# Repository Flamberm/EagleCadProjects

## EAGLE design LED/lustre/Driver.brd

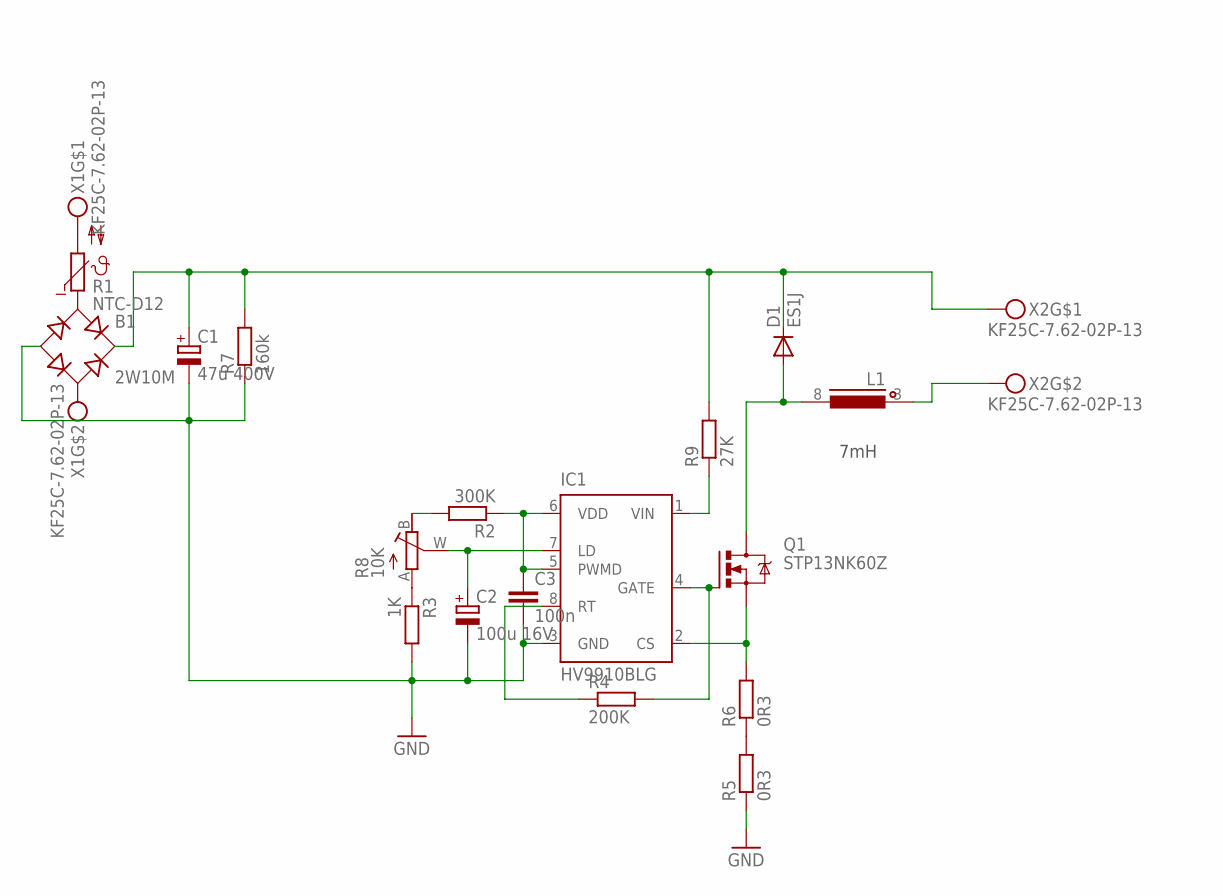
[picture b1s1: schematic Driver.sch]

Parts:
B1: 2W10M; RB1A
C1: 47u 400V; E7,5-16-32-HORIZ
C2: 100u 16V; E2,5-6
C3: 100n; C0805
D1: ES1J; DO214AC
IC1: HV9910BLG; SOIC-08LG
L1: INDUCTOREE20V; EE20_10PIN
Q1: STP13NK60Z; TO220BV
R1: NTC-D12
R2: 300K; R0805
R3: 1K; R0805
R4: 200K; R0805
R5, R6: 0R3; 0414/15
R7: 160k; 0204/7
R8: 10K; RJ9W
R9: 27K; P0613/15
X1, X2: KF25C-7.62-02P-13

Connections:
300V: B1.+, C1.+, D1.C, R7.2, R9.2, X2.P$1
GND: B1.-, C1.-, C2.-, C3.2, IC1.3 (GND), R3.2, R5.1, R7.1
unnamed: C3.1, IC1.5 (PWMD), IC1.6 (VDD), R2.1
unnamed: R1.2, X1.P$1
unnamed: B1.AC2, X1.P$2
unnamed: B1.AC1, R1.1
unnamed: L1.3 (1), X2.P$2
unnamed: C2.+, IC1.7 (LD), R8.W (S)
unnamed: D1.A, L1.8 (2), Q1.D
unnamed: IC1.8 (RT), R4.1
unnamed: IC1.4 (GATE), Q1.G, R4.2
unnamed: R5.2, R6.1
unnamed: IC1.2 (CS), Q1.S, R6.2
unnamed: R3.1, R8.A
unnamed: R2.2, R8.B (E)
unnamed: IC1.1 (VIN), R9.1

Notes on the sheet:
7mH

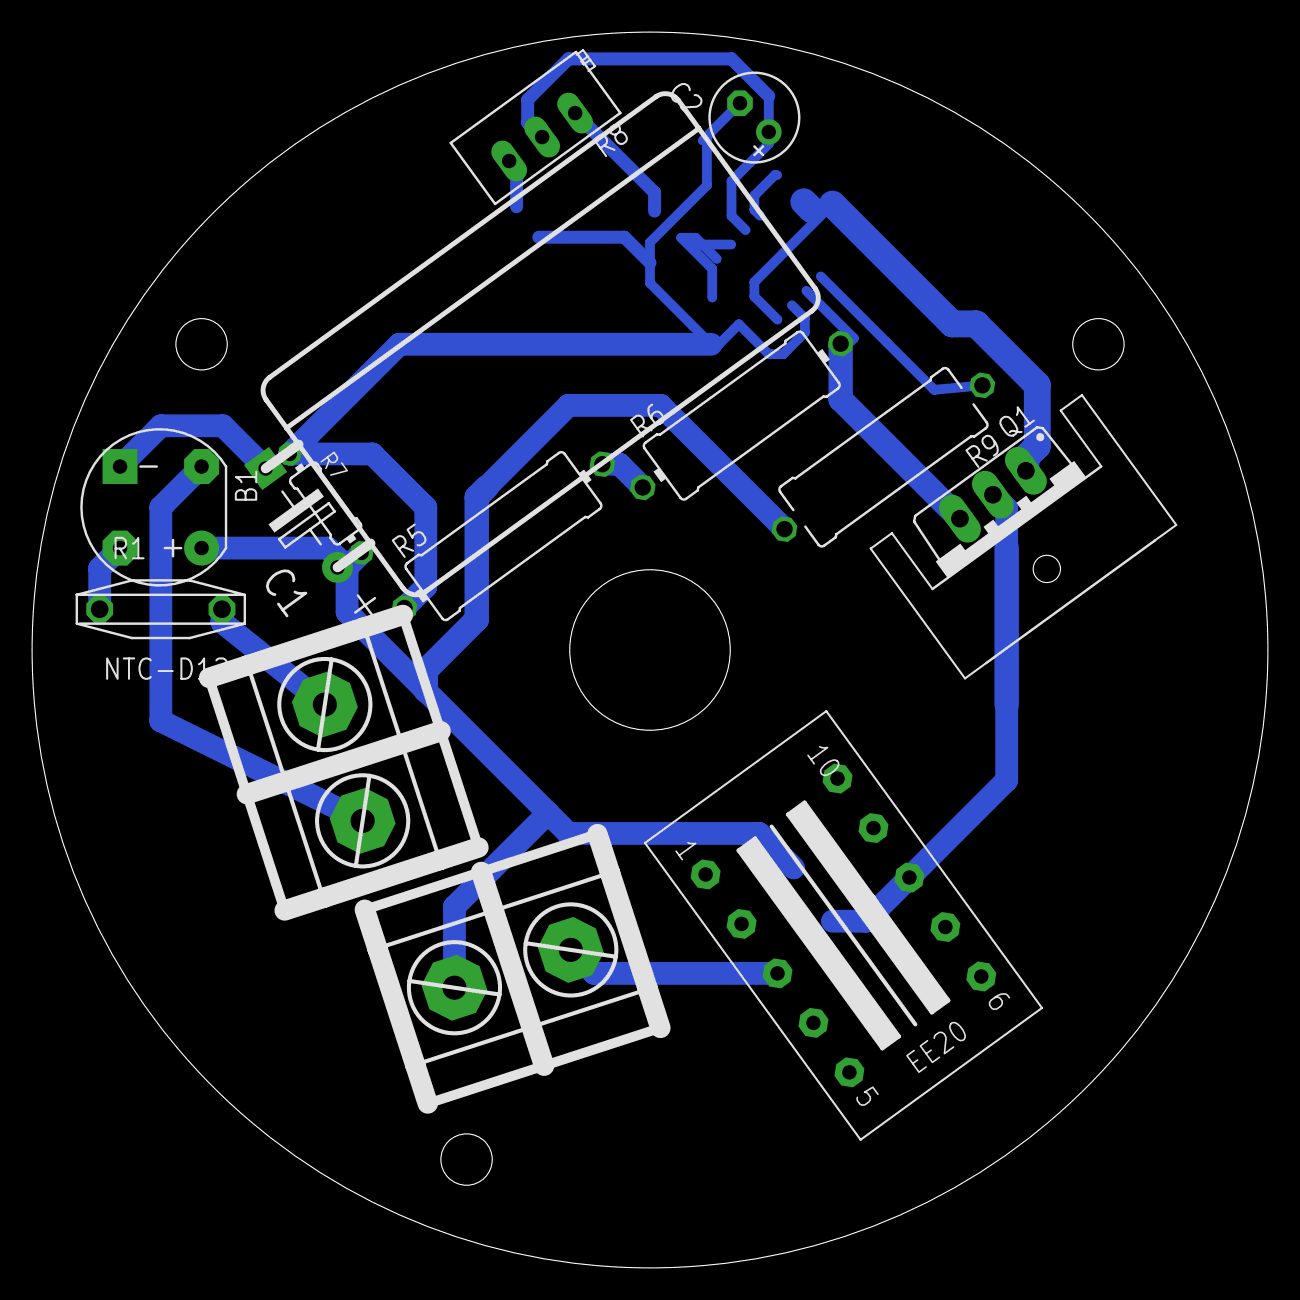
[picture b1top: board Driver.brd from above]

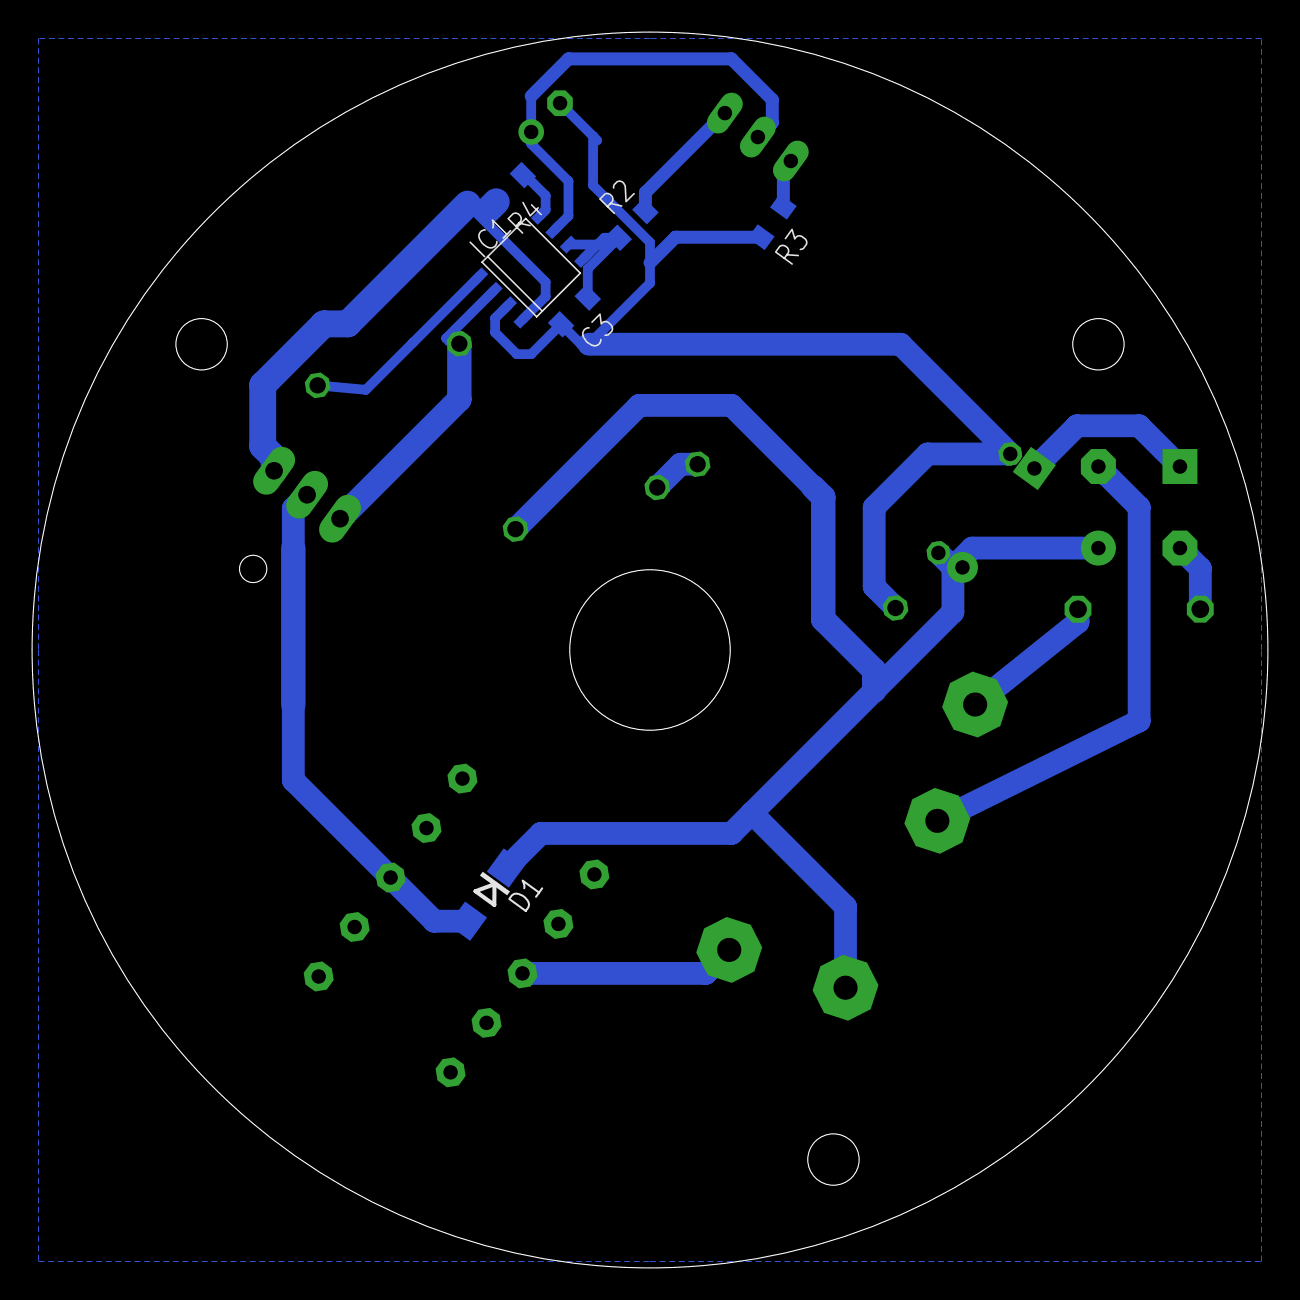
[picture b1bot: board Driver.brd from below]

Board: 2 copper layers, 77.0 x 77.0 mm, 20 parts (6 on the bottom side), 16 nets.

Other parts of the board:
U$1: SK95-3M3_HOLE

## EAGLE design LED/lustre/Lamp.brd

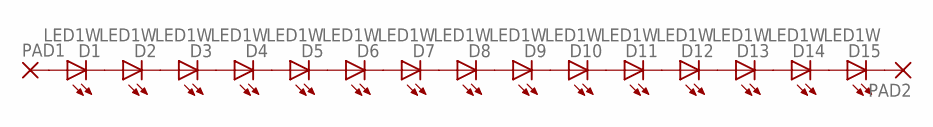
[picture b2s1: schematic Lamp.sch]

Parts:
D1, D2, D3, D4, D5, D6, D7, D8, D9, D10, D11, D12, D13, D14, D15: LED1W; LED-1W
PAD1, PAD2: 3,81/1,4

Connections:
unnamed: D1.K (C), D2.A
unnamed: D2.K (C), D3.A
unnamed: D3.K (C), D4.A
unnamed: D4.K (C), D5.A
unnamed: D5.K (C), D6.A
unnamed: D6.K (C), D7.A
unnamed: D7.K (C), D8.A
unnamed: D8.K (C), D9.A
unnamed: D9.K (C), D10.A
unnamed: D1.A, PAD1.1
unnamed: D10.K (C), D11.A
unnamed: D11.K (C), D12.A
unnamed: D12.K (C), D13.A
unnamed: D13.K (C), D14.A
unnamed: D14.K (C), D15.A
unnamed: D15.K (C), PAD2.1

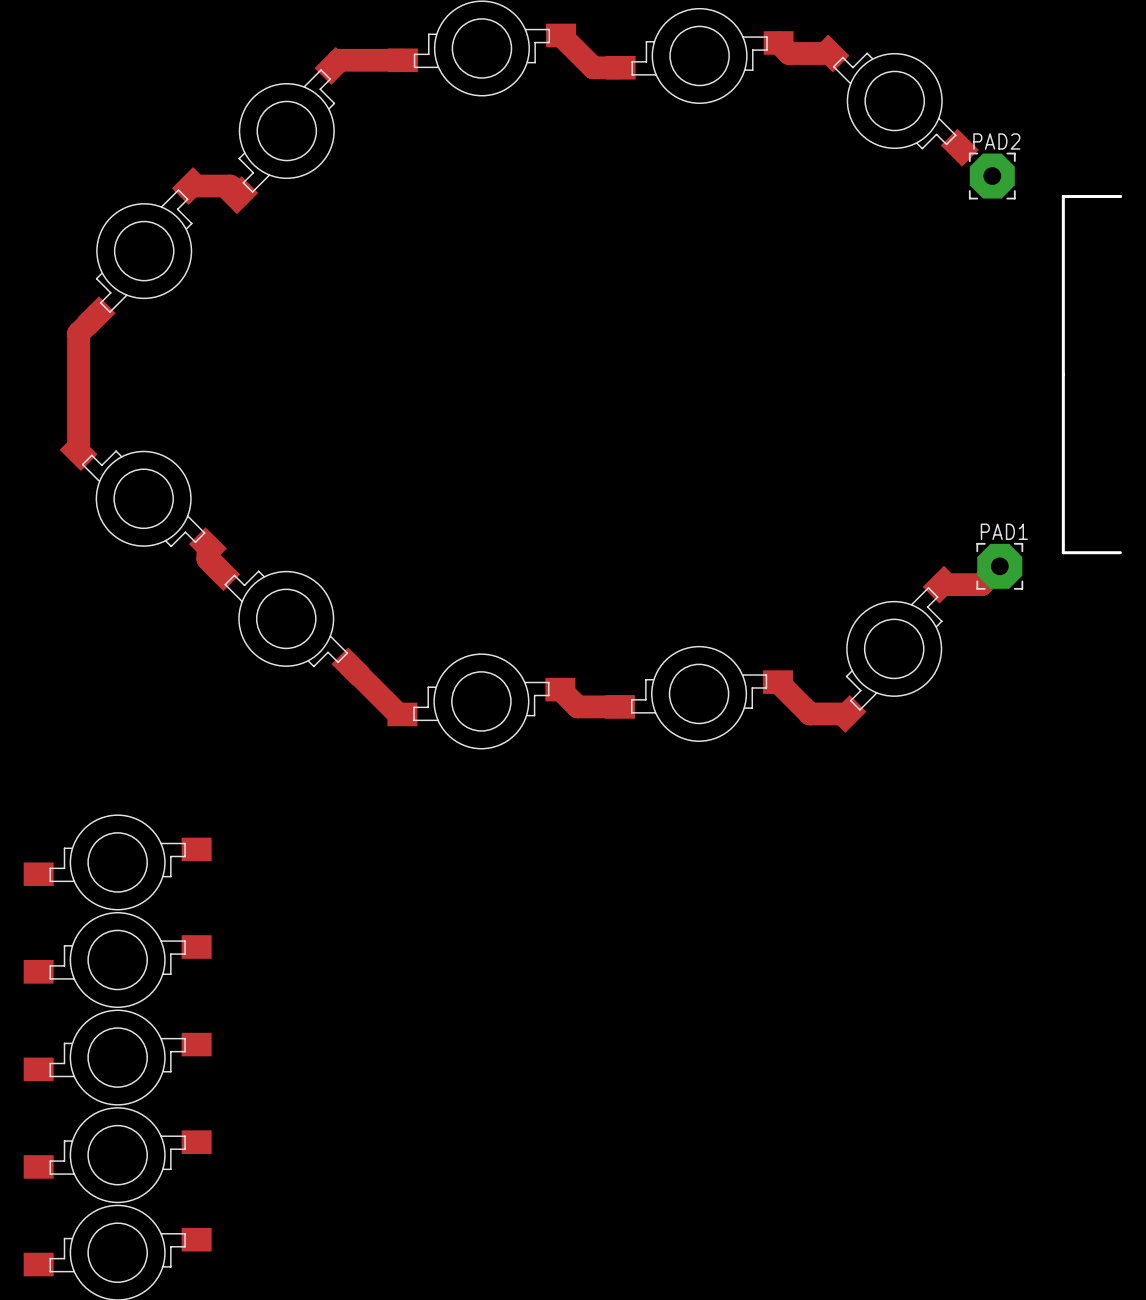
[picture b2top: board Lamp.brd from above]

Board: 2 copper layers, 17 parts (0 on the bottom side), 16 nets.

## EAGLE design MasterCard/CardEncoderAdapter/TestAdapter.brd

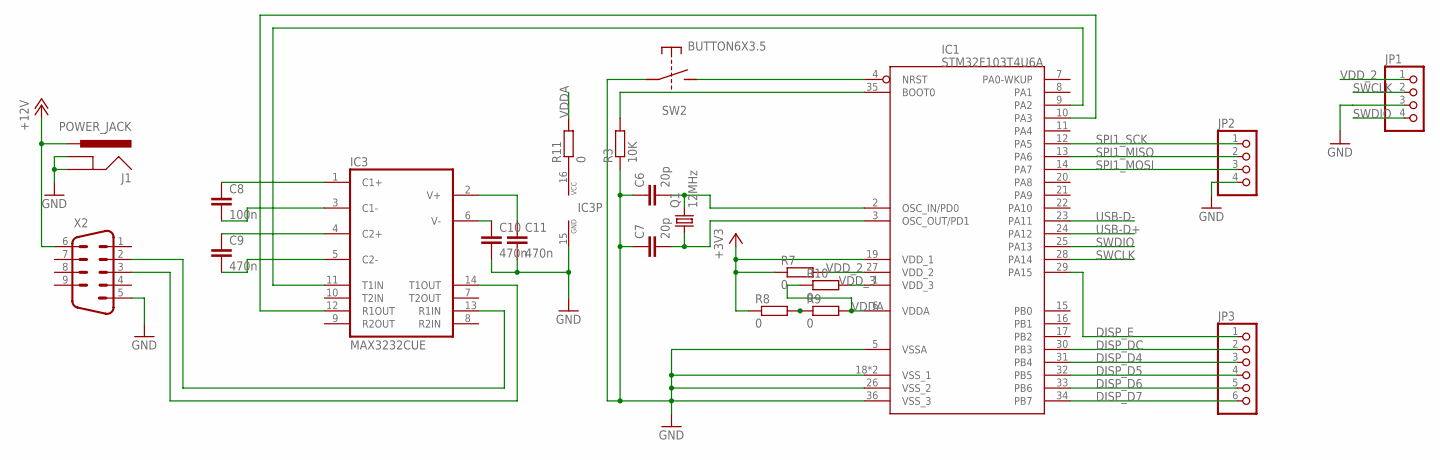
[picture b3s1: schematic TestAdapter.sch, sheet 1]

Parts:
C6, C7: 20p; CAP0805
C8: 100n; CAP0805
C9, C10, C11: 470n; CAP0805
IC1: STM32F103T4U6A; QFN50P606X606X100-36
IC3: MAX3232CUE; TSSOP16
J1: POWER_JACK; POWER_JACK_PTH
JP1, JP2: PINHD-1X4; 1X04
JP3: PINHD-1X6; 1X06
Q1: 12MHz; CRYSTAL-5025
R3: 10K; RESC2012X50
R7, R8, R9, R10, R11: 0; RESC2012X50
SW2: BUTTON6X3.5; SW-6X3.5
X2: M09-182; 182-009-MALE

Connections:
+3V3: IC1.19 (VDD_1), R7.1, R8.1; also elsewhere on the board
+12V: J1.PWR, X2.6
DISP_D4: IC1.31 (PB4), JP3.3
DISP_D5: IC1.32 (PB5), JP3.4
DISP_D6: IC1.33 (PB6), JP3.5
DISP_D7: IC1.34 (PB7), JP3.6
DISP_DC: IC1.30 (PB3), JP3.2
DISP_E: IC1.29 (PA15), JP3.1
GND: C6.1, C7.1, C10.2, C11.2, IC1.5 (VSSA), IC1.18 (VSS_1), IC1.26 (VSS_2), IC1.36 (VSS_3), IC1.P$1 (VSS_1), IC3.15 (GND), J1.GND, J1.GNDBREAK, JP1.3, JP2.4, R3.1, SW2.1, X2.5; also elsewhere on the board
unnamed: C7.2, IC1.3 (OSC_OUT/PD1), Q1.P$1 (1)
unnamed: C6.2, IC1.2 (OSC_IN/PD0), Q1.P$2 (2)
unnamed: IC1.35 (BOOT0), R3.2
unnamed: IC1.4 (NRST), SW2.2
unnamed: IC3.16 (VCC), R11.1
unnamed: R8.2, R9.1
unnamed: IC1.9 (PA2), IC3.11 (T1IN)
unnamed: IC1.10 (PA3), IC3.12 (R1OUT)
unnamed: IC3.14 (T1OUT), X2.3
unnamed: IC3.13 (R1IN), X2.2
unnamed: C8.1, IC3.1 (C1+)
unnamed: C8.2, IC3.3 (C1-)
unnamed: C9.1, IC3.4 (C2+)
unnamed: C9.2, IC3.5 (C2-)
unnamed: C11.1, IC3.2 (V+)
unnamed: C10.1, IC3.6 (V-)
SPI1_MISO: IC1.13 (PA6), JP2.2
SPI1_MOSI: IC1.14 (PA7), JP2.3
SPI1_SCK: IC1.12 (PA5), JP2.1
SWCLK: IC1.28 (PA14), JP1.2
SWDIO: IC1.25 (PA13), JP1.4
USB-D+: IC1.24 (PA12); also elsewhere on the board
USB-D-: IC1.23 (PA11); also elsewhere on the board
VDDA: IC1.6 (VDDA), R9.2, R10.1, R11.2
VDD_2: IC1.27 (VDD_2), JP1.1, R7.2; also elsewhere on the board
VDD_3: IC1.1 (VDD_3), R10.2; also elsewhere on the board

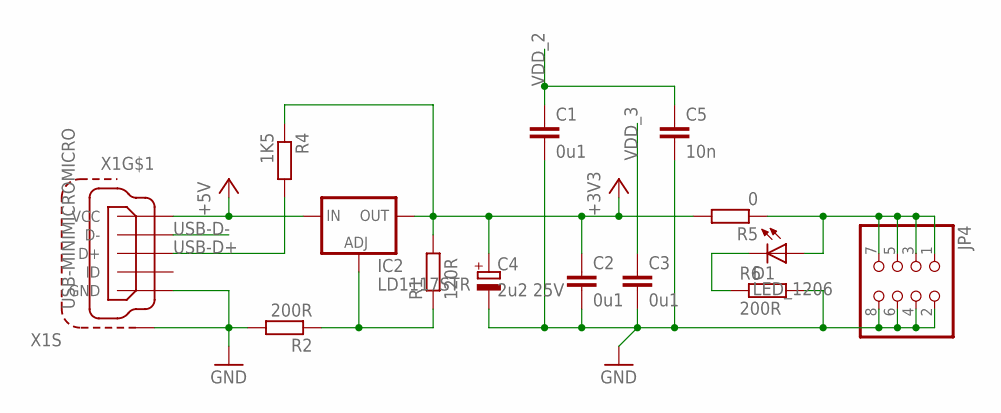
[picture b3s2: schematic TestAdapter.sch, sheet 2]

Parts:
C1, C2, C3: 0u1; CAP0805
C4: 2u2 25V; CAPMP3317X180
C5: 10n; CAP0805
D1: LED_1206; LED1206
IC2: LD1117STR; SOT230P700X180-4
JP4: PINHD-2X4; 2X04
R1: 120R; RESC2012X50
R2, R6: 200R; RESC2012X50
R4: 1K5; RESC2012X50
R5: 0; RESC2012X50
X1: USB-MINIMICROMICRO; USB-B-MICRO-SMD

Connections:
+3V3: C2.1, C4.1 (+), IC2.2 (OUT), IC2.4 (OUT), R1.2, R4.1, R5.2; also elsewhere on the board
+5V: IC2.3 (IN), X1.VBUS (VCC)
GND: C1.2, C2.2, C3.2, C4.2 (-), C5.2, JP4.2, JP4.4, JP4.6, JP4.8, R2.2, R6.2, X1.GND, X1.SHIELD1 (S1), X1.SHIELD2 (S1), X1.SHIELD3 (S1); also elsewhere on the board
unnamed: IC2.1 (ADJ), R1.1, R2.1
unnamed: D1.A, JP4.1, JP4.3, JP4.5, JP4.7, R5.1
unnamed: D1.C, R6.1
USB-D+: R4.2, X1.D+; also elsewhere on the board
USB-D-: X1.D-; also elsewhere on the board
VDD_2: C1.1, C5.1; also elsewhere on the board
VDD_3: C3.1; also elsewhere on the board

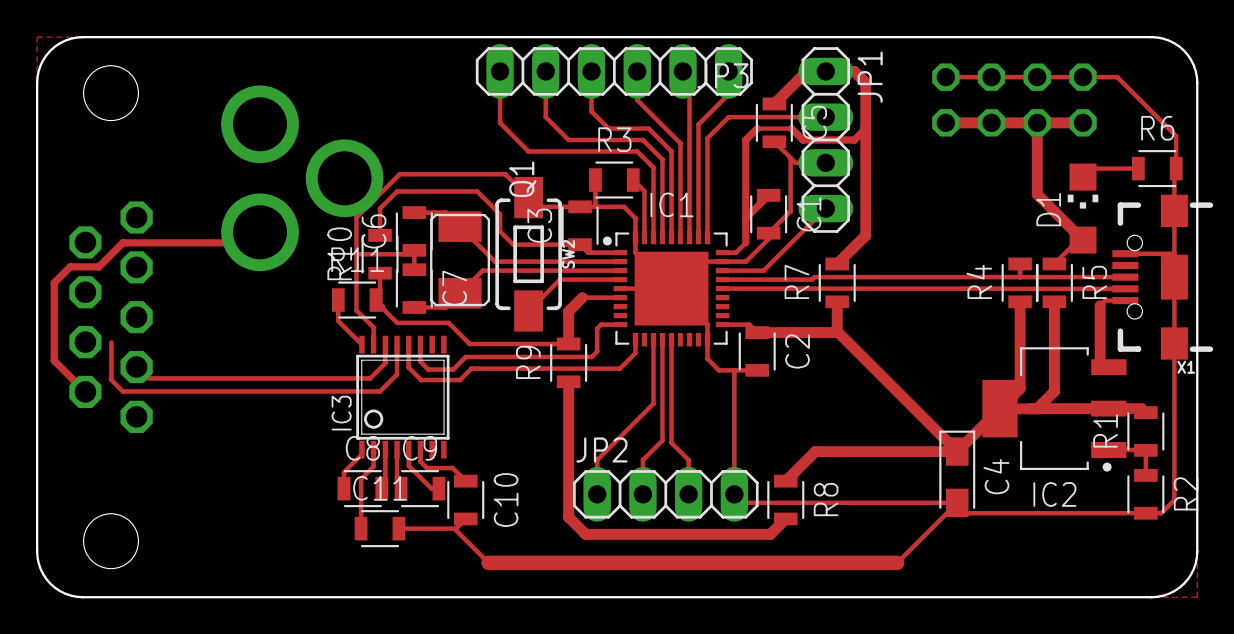
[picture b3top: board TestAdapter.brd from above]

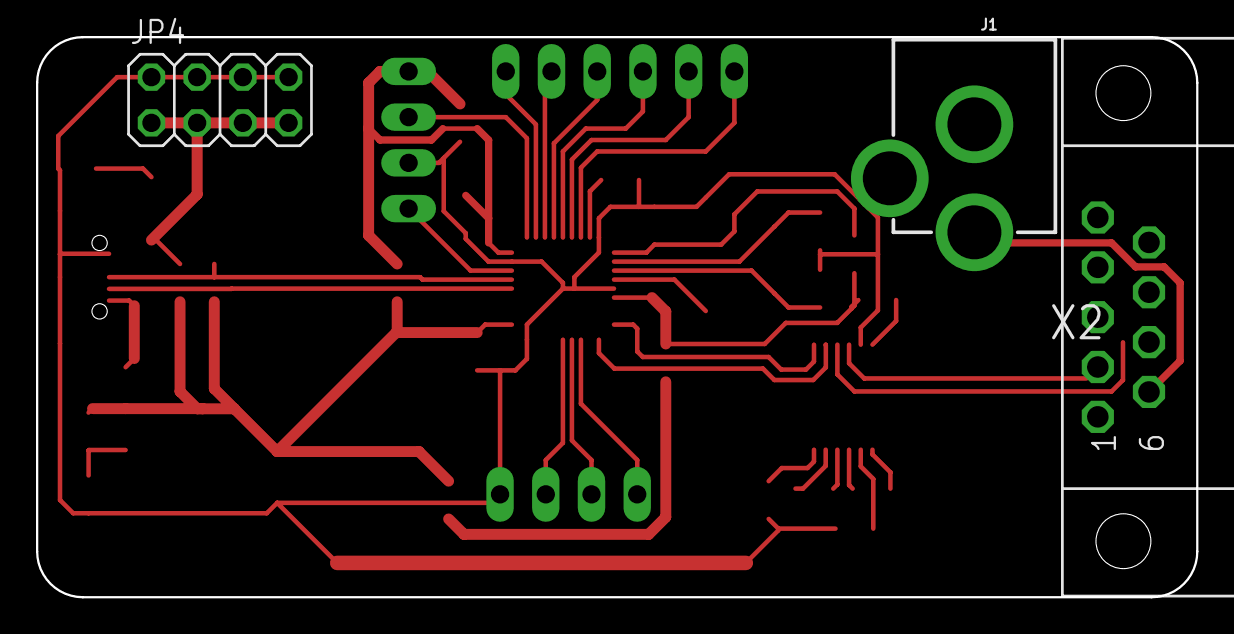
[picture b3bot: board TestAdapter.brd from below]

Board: 2 copper layers, 64.5 x 31.1 mm, 35 parts (3 on the bottom side), 39 nets.

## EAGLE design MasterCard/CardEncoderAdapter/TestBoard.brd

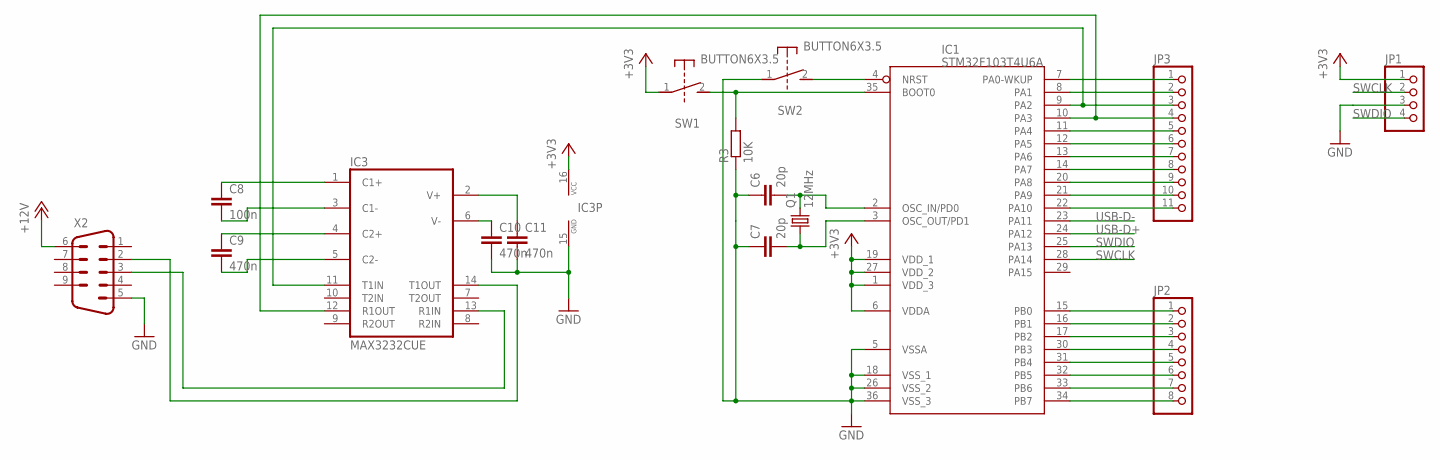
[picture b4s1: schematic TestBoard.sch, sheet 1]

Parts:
C6, C7: 20p; CAP0805
C8: 100n; CAP0805
C9, C10, C11: 470n; CAP0805
IC1: STM32F103T4U6A; QFN50P606X606X100-36
IC3: MAX3232CUE; TSSOP16
JP1: PINHD-1X4; 1X04
JP2: PINHD-1X8; 1X08
JP3: PINHD-1X11; 1X11
Q1: 12MHz; HC49UP
R3: 10K; RESC2012X50
SW1, SW2: BUTTON6X3.5; SW-6X3.5
X2: M09-182; 182-009-MALE

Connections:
+3V3: IC1.1 (VDD_3), IC1.6 (VDDA), IC1.19 (VDD_1), IC1.27 (VDD_2), IC3.16 (VCC), JP1.1, SW1.1; also elsewhere on the board
+12V: X2.6
GND: C6.1, C7.1, C10.2, C11.2, IC1.5 (VSSA), IC1.18 (VSS_1), IC1.26 (VSS_2), IC1.36 (VSS_3), IC3.15 (GND), JP1.3, R3.1, SW2.1, X2.5; also elsewhere on the board
unnamed: C7.2, IC1.3 (OSC_OUT/PD1), Q1.1
unnamed: C6.2, IC1.2 (OSC_IN/PD0), Q1.2
unnamed: IC1.35 (BOOT0), R3.2, SW1.2
unnamed: IC1.4 (NRST), SW2.2
unnamed: IC1.15 (PB0), JP2.1
unnamed: IC1.16 (PB1), JP2.2
unnamed: IC1.17 (PB2), JP2.3
unnamed: IC1.30 (PB3), JP2.4
unnamed: IC1.31 (PB4), JP2.5
unnamed: IC1.32 (PB5), JP2.6
unnamed: IC1.33 (PB6), JP2.7
unnamed: IC1.34 (PB7), JP2.8
unnamed: IC1.7 (PA0-WKUP), JP3.1
unnamed: IC1.8 (PA1), JP3.2
unnamed: IC1.9 (PA2), IC3.11 (T1IN), JP3.3
unnamed: IC1.10 (PA3), IC3.12 (R1OUT), JP3.4
unnamed: IC1.11 (PA4), JP3.5
unnamed: IC1.12 (PA5), JP3.6
unnamed: IC1.13 (PA6), JP3.7
unnamed: IC1.14 (PA7), JP3.8
unnamed: IC1.20 (PA8), JP3.9
unnamed: IC1.21 (PA9), JP3.10
unnamed: IC1.22 (PA10), JP3.11
unnamed: IC3.14 (T1OUT), X2.2
unnamed: IC3.13 (R1IN), X2.3
unnamed: C8.1, IC3.1 (C1+)
unnamed: C8.2, IC3.3 (C1-)
unnamed: C9.1, IC3.4 (C2+)
unnamed: C9.2, IC3.5 (C2-)
unnamed: C11.1, IC3.2 (V+)
unnamed: C10.1, IC3.6 (V-)
SWCLK: IC1.28 (PA14), JP1.2
SWDIO: IC1.25 (PA13), JP1.4
USB-D+: IC1.24 (PA12); also elsewhere on the board
USB-D-: IC1.23 (PA11); also elsewhere on the board

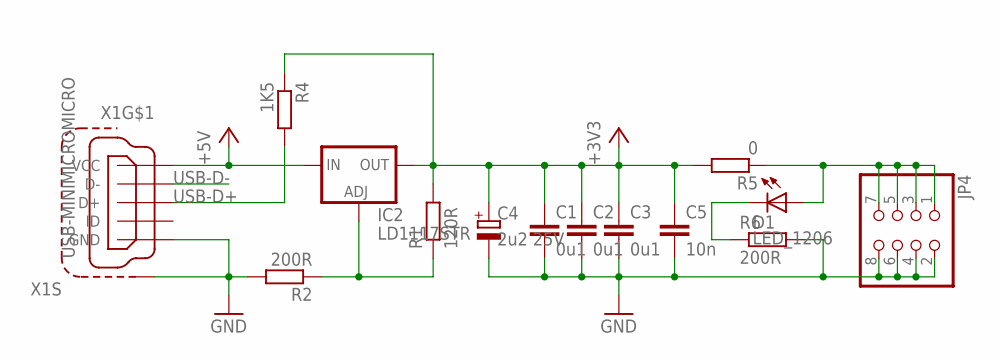
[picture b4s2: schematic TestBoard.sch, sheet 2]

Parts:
C1, C2, C3: 0u1; CAP0805
C4: 2u2 25V; CAPMP3317X180
C5: 10n; CAP0805
D1: LED_1206; LED1206
IC2: LD1117STR; SOT230P700X180-4
JP4: PINHD-2X4; 2X04
R1: 120R; RESC2012X50
R2, R6: 200R; RESC2012X50
R4: 1K5; RESC2012X50
R5: 0; RESC2012X50
X1: USB-MINIMICROMICRO; USB-B-MICRO-SMD

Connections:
+3V3: C1.1, C2.1, C3.1, C4.1 (+), C5.1, IC2.2 (OUT), IC2.4 (OUT), R1.2, R4.1, R5.2; also elsewhere on the board
+5V: IC2.3 (IN), X1.VBUS (VCC)
GND: C1.2, C2.2, C3.2, C4.2 (-), C5.2, JP4.2, JP4.4, JP4.6, JP4.8, R2.2, R6.2, X1.GND, X1.SHIELD1 (S1), X1.SHIELD2 (S1), X1.SHIELD3 (S1); also elsewhere on the board
unnamed: IC2.1 (ADJ), R1.1, R2.1
unnamed: D1.A, JP4.1, JP4.3, JP4.5, JP4.7, R5.1
unnamed: D1.C, R6.1
USB-D+: R4.2, X1.D+; also elsewhere on the board
USB-D-: X1.D-; also elsewhere on the board

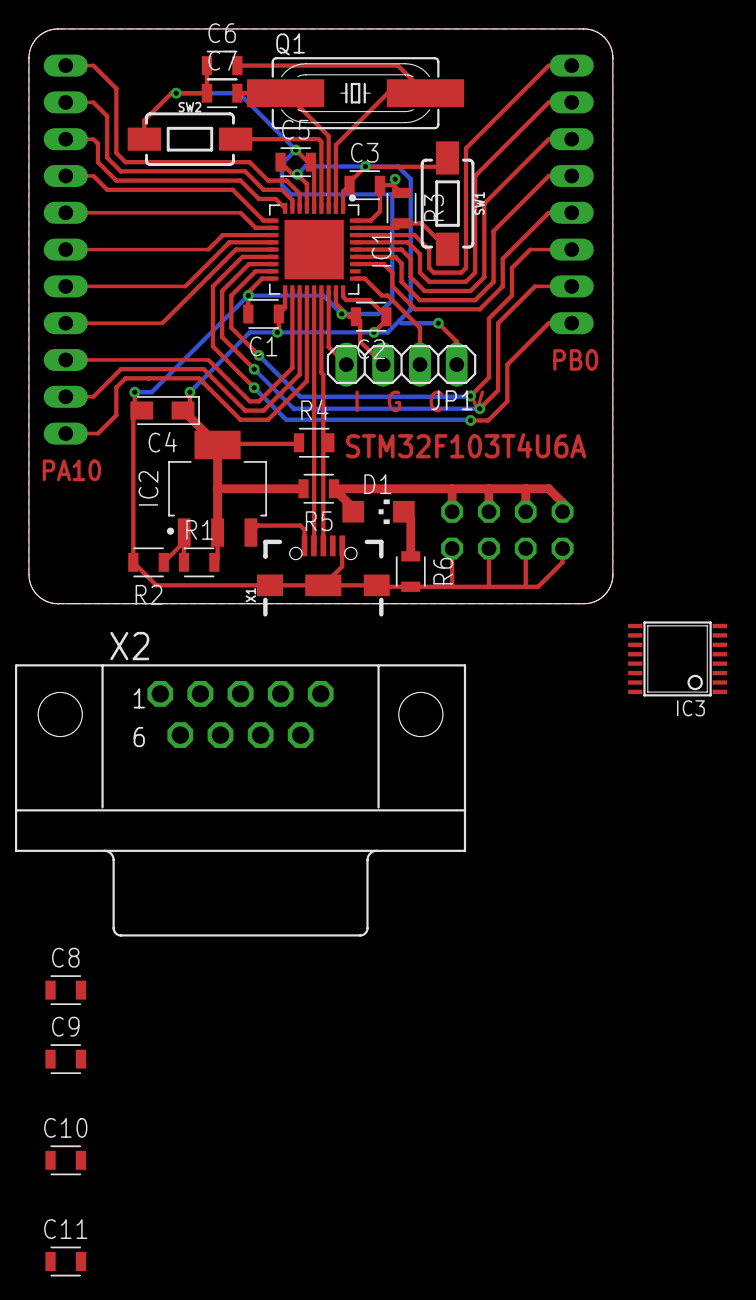
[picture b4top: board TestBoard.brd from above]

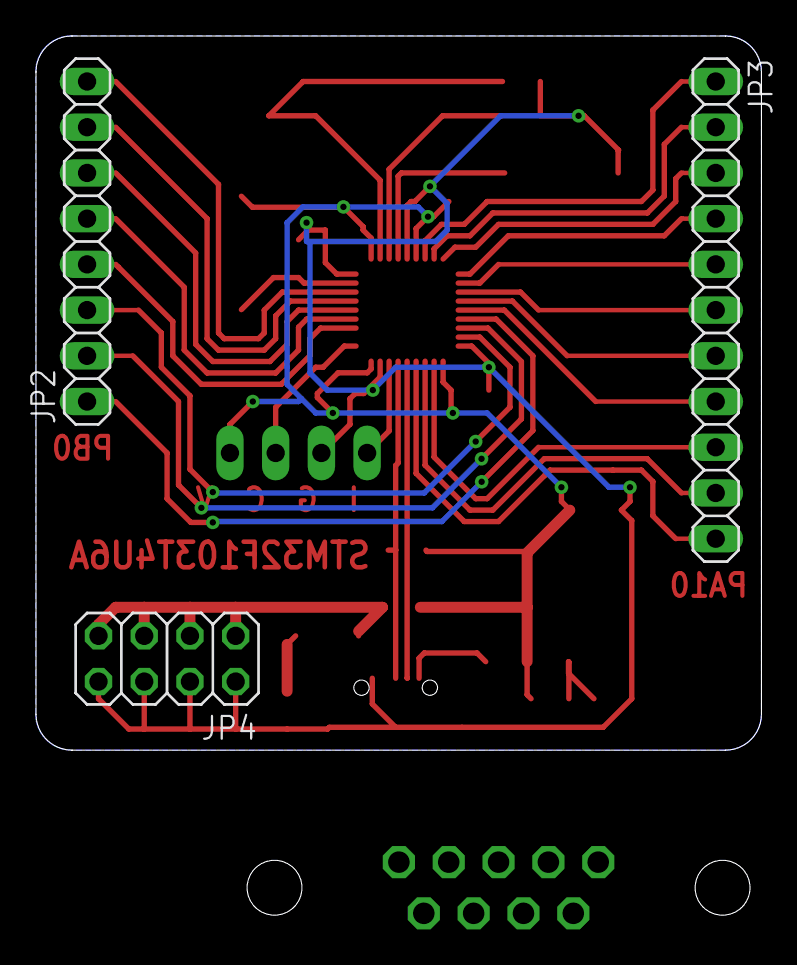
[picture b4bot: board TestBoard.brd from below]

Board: 2 copper layers, 40.3 x 39.7 mm, 30 parts (3 on the bottom side), 41 nets.

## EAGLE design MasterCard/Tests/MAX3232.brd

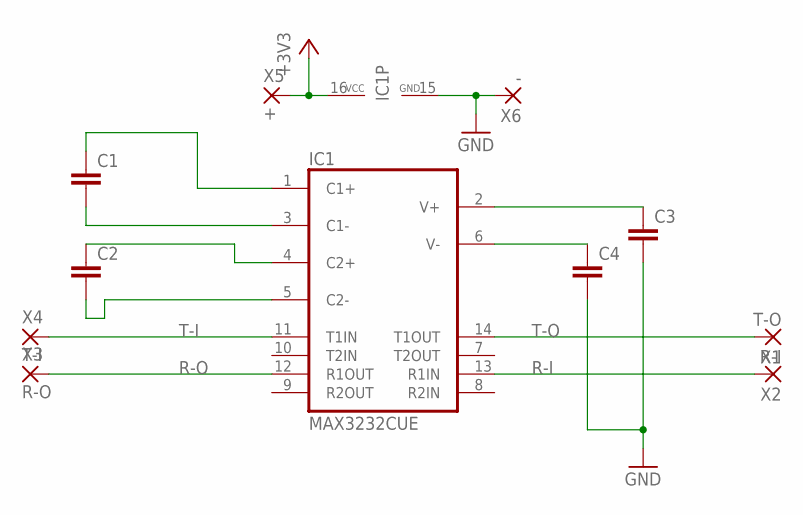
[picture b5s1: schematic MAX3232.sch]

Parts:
C1, C2, C3, C4: CAP_0805; CAP0805
IC1: MAX3232CUE; TSSOP16
X1: T-O; PAD-1.27X2.54
X2: R-I; PAD-1.27X2.54
X3: R-O; PAD-1.27X2.54
X4: T-I; PAD-1.27X2.54
X5: +; PAD-1.27X2.54
X6: -; PAD-1.27X2.54

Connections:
+3V3: IC1.16 (VCC), X5.P$1
GND: C3.2, C4.2, IC1.15 (GND), X6.P$1
unnamed: C1.1, IC1.1 (C1+)
unnamed: C1.2, IC1.3 (C1-)
unnamed: C2.1, IC1.4 (C2+)
unnamed: C2.2, IC1.5 (C2-)
unnamed: C4.1, IC1.6 (V-)
unnamed: C3.1, IC1.2 (V+)
R-I: IC1.13 (R1IN), X2.P$1
R-O: IC1.12 (R1OUT), X3.P$1
T-I: IC1.11 (T1IN), X4.P$1
T-O: IC1.14 (T1OUT), X1.P$1

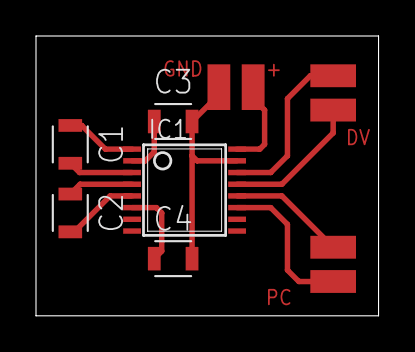
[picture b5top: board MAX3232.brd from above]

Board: 2 copper layers, 19.0 x 15.5 mm, 11 parts (0 on the bottom side), 12 nets.

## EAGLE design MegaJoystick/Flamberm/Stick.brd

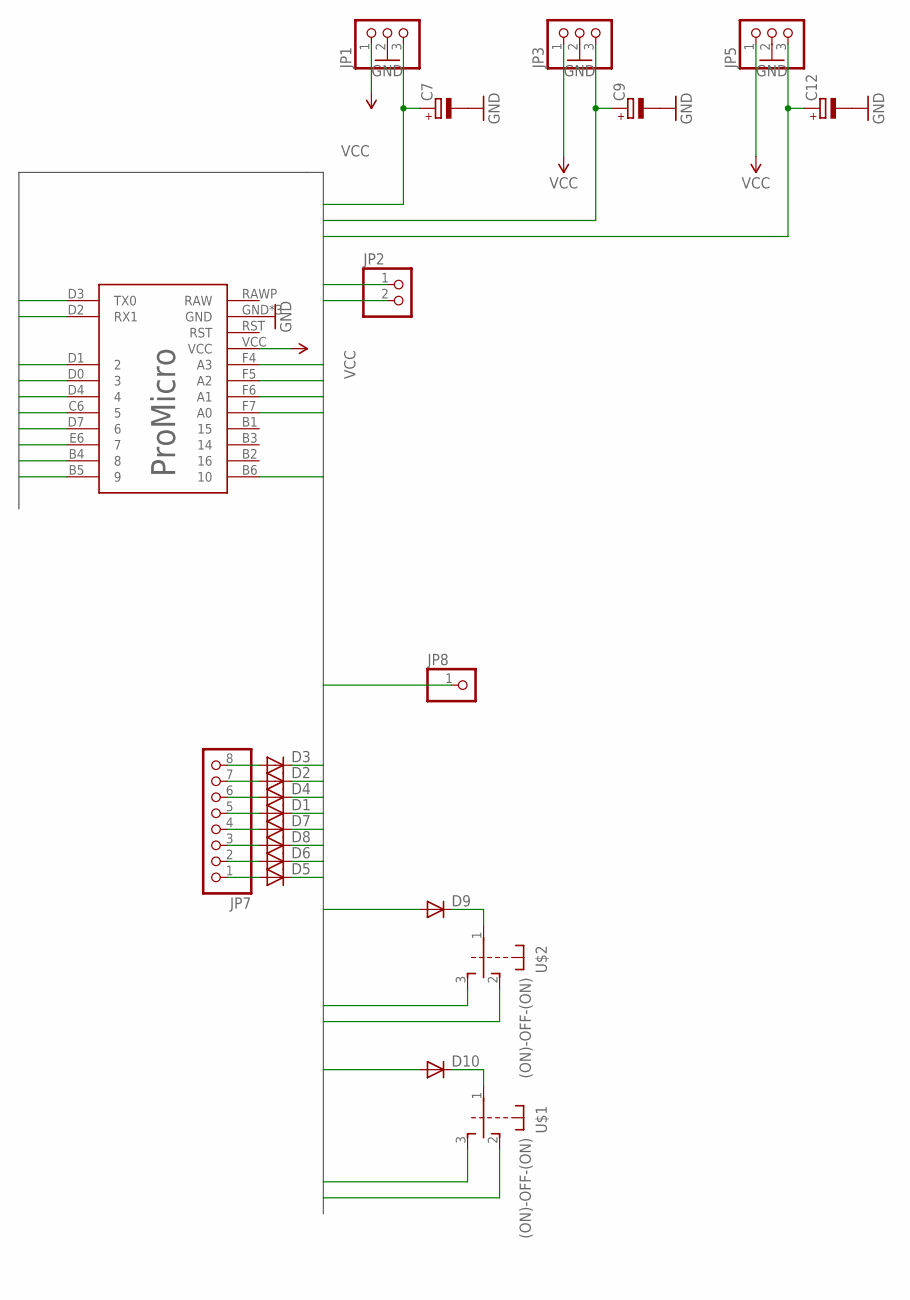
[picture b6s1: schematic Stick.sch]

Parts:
C7, C9, C12: CPOL-EUE2.5-5; E2,5-5
D1, D2, D3, D4, D5, D6, D7, D8, D9, D10: DIODE-MINIMELF; MINIMELF
JP1, JP3, JP5: PINHD-1X3; 1X03
JP2: PINHD-1X2; 1X02
JP7: PINHD-1X8; 1X08
JP8: PINHD-1X1; 1X01
U$1, U$2: (ON)-OFF-(ON); SWITCH-(ON)-OFF-(ON)
U$3: SPARKFUN; PRO-MICRO

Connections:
A1: C7.+, JP1.3, U$3.F4 (A3)
A2: C9.+, JP3.3, U$3.F5 (A2)
A3: C12.+, JP5.3, U$3.F6 (A1)
A4: JP2.1, U$3.F7 (A0)
A5: JP2.2, U$3.B6 (10)
C1: JP8.1, U$3.D2 (RX1)
C2: D9.A, D10.A, U$3.D3 (TX0)
GND: C7.-, C9.-, C12.-, JP1.2, JP3.2, JP5.2, U$3.GND, U$3.GND3 (GND), U$3.GND4 (GND)
unnamed: D9.C, U$2.1
unnamed: D10.C, U$1.1
unnamed: D8.A, JP7.3
unnamed: D7.A, JP7.4
unnamed: D6.A, JP7.2
unnamed: D5.A, JP7.1
unnamed: D4.A, JP7.6
unnamed: D3.A, JP7.8
unnamed: D2.A, JP7.7
unnamed: D1.A, JP7.5
R1: D5.C, U$3.D1 (2)
R2: D6.C, U$2.2, U$3.D0 (3)
R3: D8.C, U$2.3, U$3.D4 (4)
R4: D7.C, U$1.2, U$3.C6 (5)
R5: D1.C, U$1.3, U$3.D7 (6)
R6: D4.C, U$3.E6 (7)
R7: D2.C, U$3.B4 (8)
R8: D3.C, U$3.B5 (9)
VCC: JP1.1, JP3.1, JP5.1, U$3.VCC

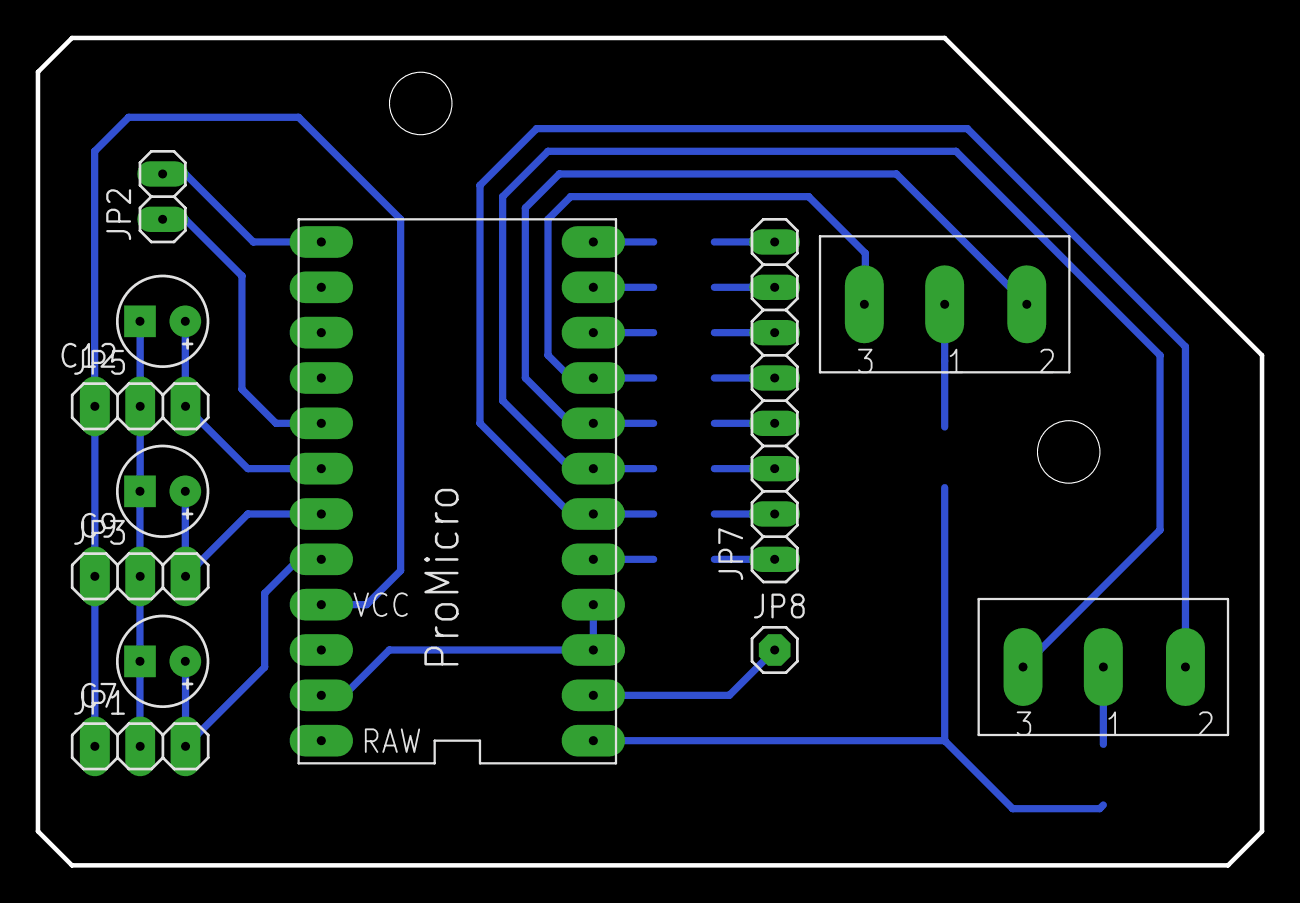
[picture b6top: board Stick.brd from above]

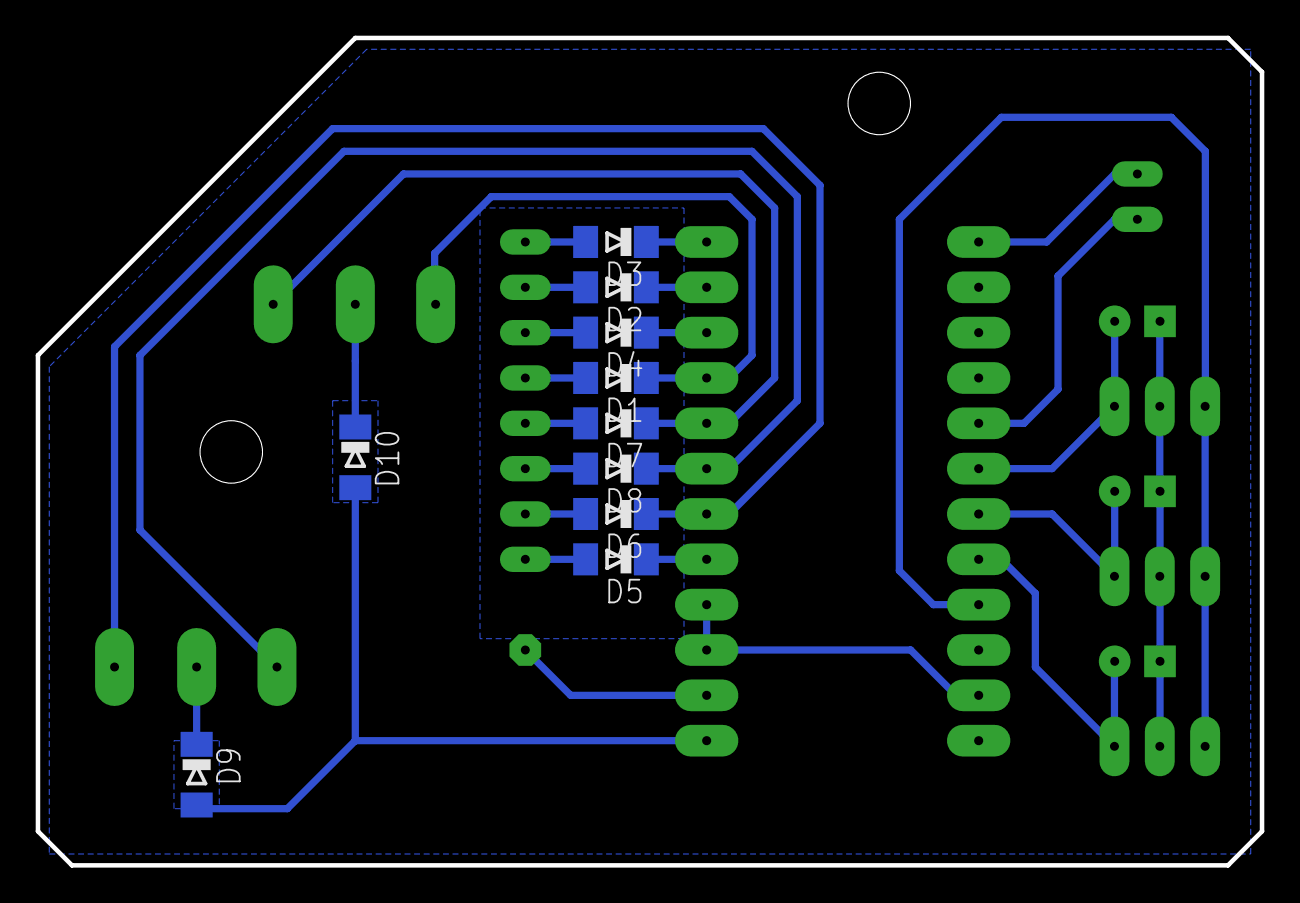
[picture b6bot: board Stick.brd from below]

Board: 2 copper layers, 68.6 x 46.4 mm, 22 parts (10 on the bottom side), 27 nets.

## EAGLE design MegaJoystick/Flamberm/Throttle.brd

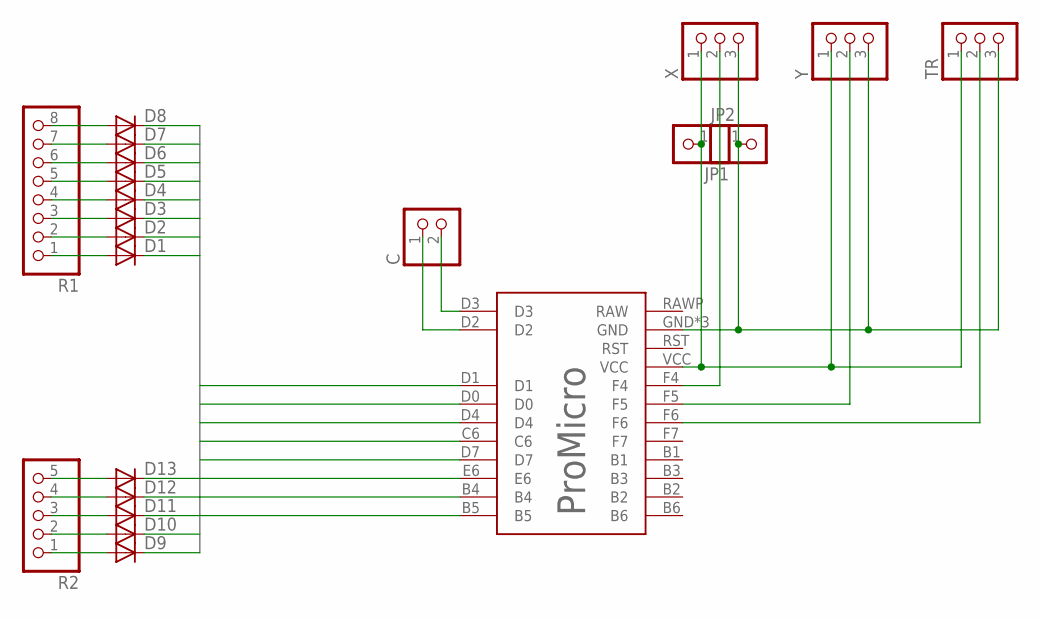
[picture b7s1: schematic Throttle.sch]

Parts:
C: PINHD-1X2; 1X02
D1, D2, D3, D4, D5, D6, D7, D8, D9, D10, D11, D12, D13: DIODE-MINIMELF; MINIMELF
JP1, JP2: PINHD-1X1; 1X01
R1: PINHD-1X8; 1X08
R2: PINHD-1X5; 1X05
TR: PINHD-1X3; 1X03
U$1: SPARKFUN; PRO-MICRO
X: PINHD-1X3; 1X03
Y: PINHD-1X3; 1X03

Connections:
unnamed: C.1, U$1.D2
unnamed: C.2, U$1.D3
unnamed: D1.A, R1.1
unnamed: D2.A, R1.2
unnamed: D3.A, R1.3
unnamed: D4.A, R1.4
unnamed: D5.A, R1.5
unnamed: D6.A, R1.6
unnamed: D7.A, R1.7
unnamed: D8.A, R1.8
unnamed: D9.A, R2.1
unnamed: D10.A, R2.2
unnamed: D11.A, R2.3
unnamed: D12.A, R2.4
unnamed: D13.A, R2.5
unnamed: JP1.1, TR.1, U$1.VCC, X.1, Y.1
unnamed: JP2.1, TR.3, U$1.GND, U$1.GND3 (GND), U$1.GND4 (GND), X.3, Y.3
unnamed: U$1.F4, X.2
unnamed: U$1.F5, Y.2
unnamed: TR.2, U$1.F6
R1: D1.C, D9.C, U$1.B5
R2: D2.C, D10.C, U$1.B4
R3: D3.C, D11.C, U$1.E6
R4: D4.C, D12.C, U$1.D7
R5: D5.C, D13.C, U$1.C6
R6: D6.C, U$1.D4
R7: D7.C, U$1.D0
R8: D8.C, U$1.D1

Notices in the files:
parts and their libraries:
SparkFun-Connectors: Licensing: Creative Commons ShareAlike 4.0 International - https://creativecommons.org/licenses/by-sa/4.0
SparkFun-Aesthetics: Licensing: CC v3.0 Share-Alike You are welcome to use this library for commercial purposes.
SparkFun-Aesthetics: Released under the Creative Commons
